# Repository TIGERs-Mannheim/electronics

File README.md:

# TIGERs Mannheim Open-Source Electronics

This repository contains electronics for our robots and our base station. There is one folder for each released version.  
Have a look at our [2020 ETDP](https://tigers-mannheim.de/download/tdps/2020_ETDP_TIGERS.pdf) which contains many details about design decisions and lessons learned over the last 10 years.

The following files are present for each release.

### EAGLE
Electronics are designed with [Autodesk EAGLE](https://www.autodesk.com/education/free-software/eagle) which is available for free for students.
This folder contains all schematics (.sch) and board (.brd) files.

### KiCad9
EAGLE files converted to KiCad version 9. Files got only a light cleanup pass.
Note that no PCBs were ever produced using these files. The EAGLE files are still the ground truth.

### PDF
All schematics are also available as PDF files. This makes it easier to view them without a need to install EAGLE.

### CAM
CAM jobs for EAGLE. Used to produce manufacturing data from board files.

### Gerber
Production ready zip packages for all boards. Most PCB production services directly accept gerber files.

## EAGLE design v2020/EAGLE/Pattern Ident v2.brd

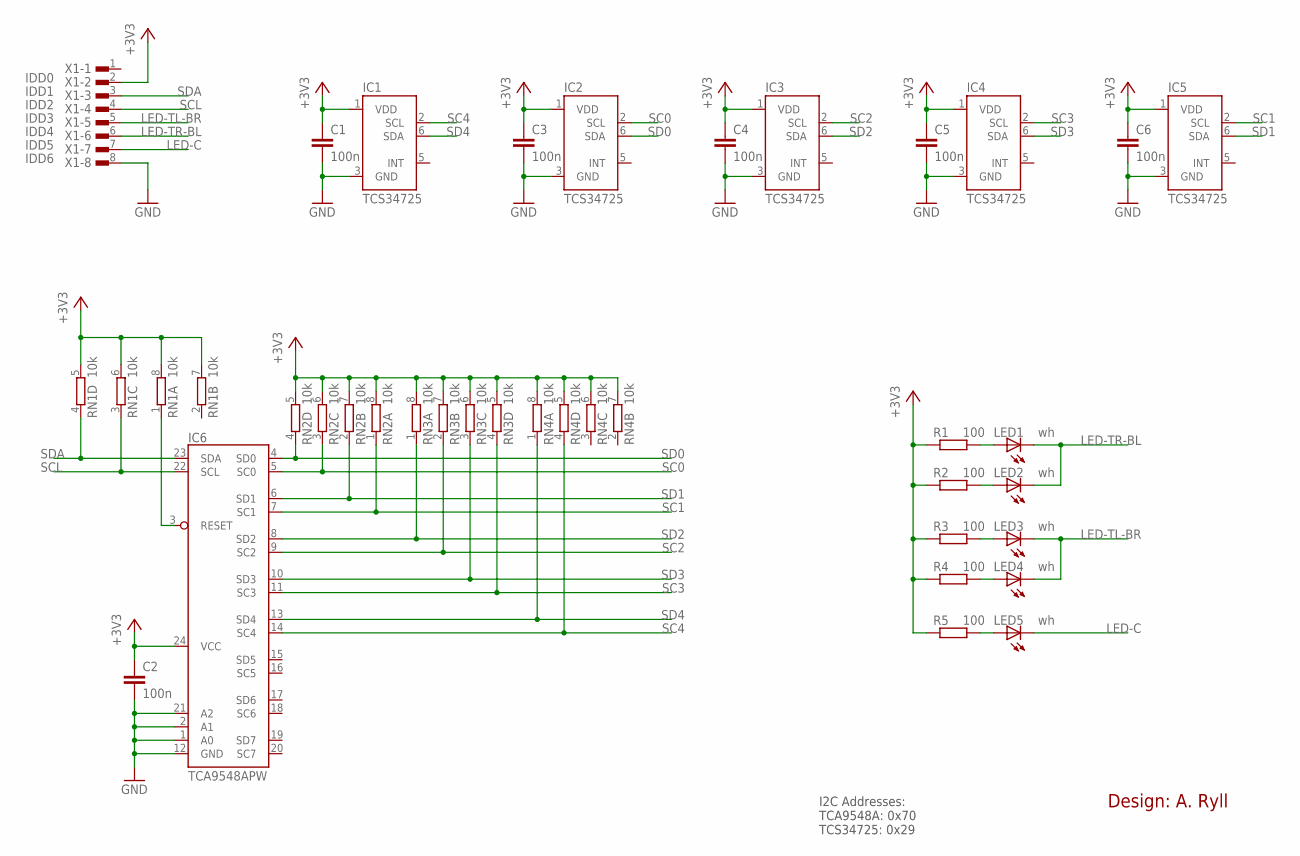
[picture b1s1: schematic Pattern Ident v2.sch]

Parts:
C1, C2, C3, C4, C5, C6: 100n; C0603
IC1, IC2, IC3, IC4, IC5: TCS34725; DFN6
IC6: TCA9548APW; TSSOP24
LED1, LED2, LED3, LED4, LED5: wh; CHIPLED_1206
R1, R2, R3, R4, R5: 100; R0603
RN1, RN2, RN3, RN4: 10k; EXB28V
X1: TE-FPC-1MM-8H; TE-84952-8

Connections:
+3V3: C1.1, C2.1, C3.1, C4.1, C5.1, C6.1, IC1.1 (VDD), IC2.1 (VDD), IC3.1 (VDD), IC4.1 (VDD), IC5.1 (VDD), IC6.24 (VCC), R1.1, R2.1, R3.1, R4.1, R5.1, RN1.5 (2), RN1.6 (2), RN1.7 (2), RN1.8 (2), RN2.5 (2), RN2.6 (2), RN2.7 (2), RN2.8 (2), RN3.5 (2), RN3.6 (2), RN3.7 (2), RN3.8 (2), RN4.5 (2), RN4.6 (2), RN4.7 (2), RN4.8 (2), X1.2
GND: C1.2, C2.2, C3.2, C4.2, C5.2, C6.2, IC1.3 (GND), IC2.3 (GND), IC3.3 (GND), IC4.3 (GND), IC5.3 (GND), IC6.1 (A0), IC6.2 (A1), IC6.12 (GND), IC6.21 (A2), X1.8
LED-C: LED5.C, X1.7
LED-TL-BR: LED3.C, LED4.C, X1.5
LED-TR-BL: LED1.C, LED2.C, X1.6
unnamed: LED1.A, R1.2
unnamed: LED2.A, R2.2
unnamed: LED3.A, R3.2
unnamed: LED4.A, R4.2
unnamed: LED5.A, R5.2
RESET: IC6.3 (RESET), RN1.1
SC0: IC2.2 (SCL), IC6.5 (SC0), RN2.3 (1)
SC1: IC5.2 (SCL), IC6.7 (SC1), RN2.1
SC2: IC3.2 (SCL), IC6.9 (SC2), RN3.2 (1)
SC3: IC4.2 (SCL), IC6.11 (SC3), RN3.4 (1)
SC4: IC1.2 (SCL), IC6.14 (SC4), RN4.4 (1)
SCL: IC6.22 (SCL), RN1.3 (1), X1.4
SD0: IC2.6 (SDA), IC6.4 (SD0), RN2.4 (1)
SD1: IC5.6 (SDA), IC6.6 (SD1), RN2.2 (1)
SD2: IC3.6 (SDA), IC6.8 (SD2), RN3.1
SD3: IC4.6 (SDA), IC6.10 (SD3), RN3.3 (1)
SD4: IC1.6 (SDA), IC6.13 (SD4), RN4.1
SDA: IC6.23 (SDA), RN1.4 (1), X1.3

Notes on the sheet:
I2C Addresses: TCA9548A: 0x70 TCS34725: 0x29
Design: A. Ryll

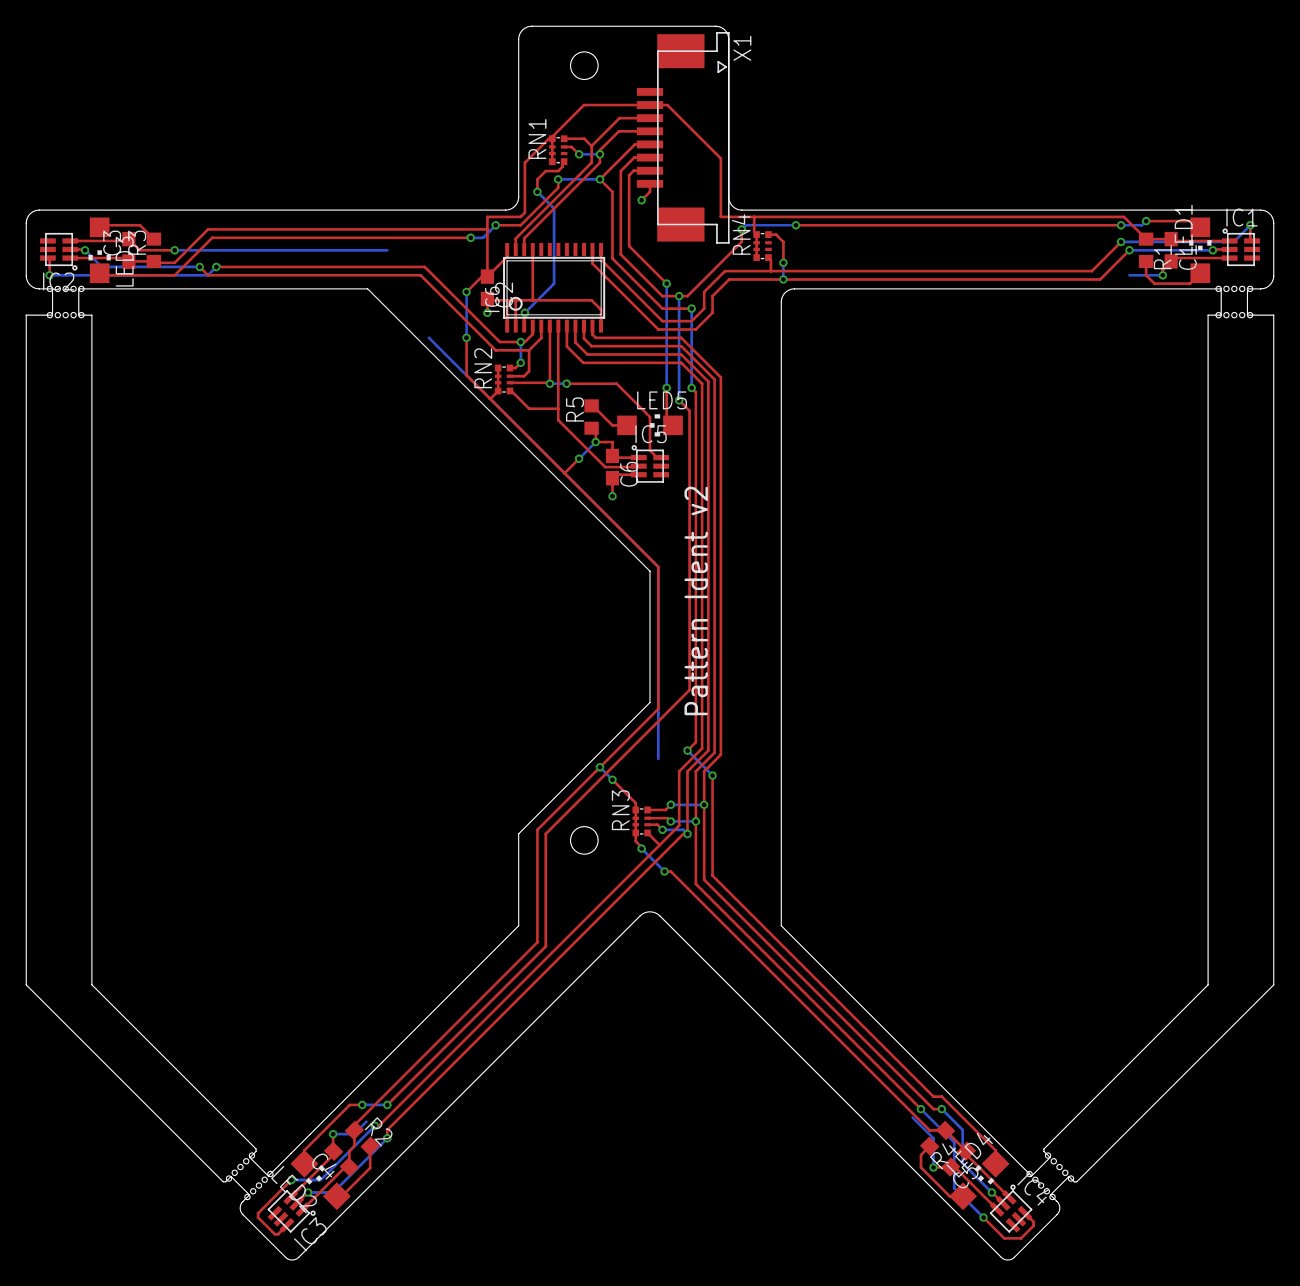
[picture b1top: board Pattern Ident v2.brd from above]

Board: 2 copper layers, 95.0 x 94.0 mm, 27 parts (0 on the bottom side), 23 nets.

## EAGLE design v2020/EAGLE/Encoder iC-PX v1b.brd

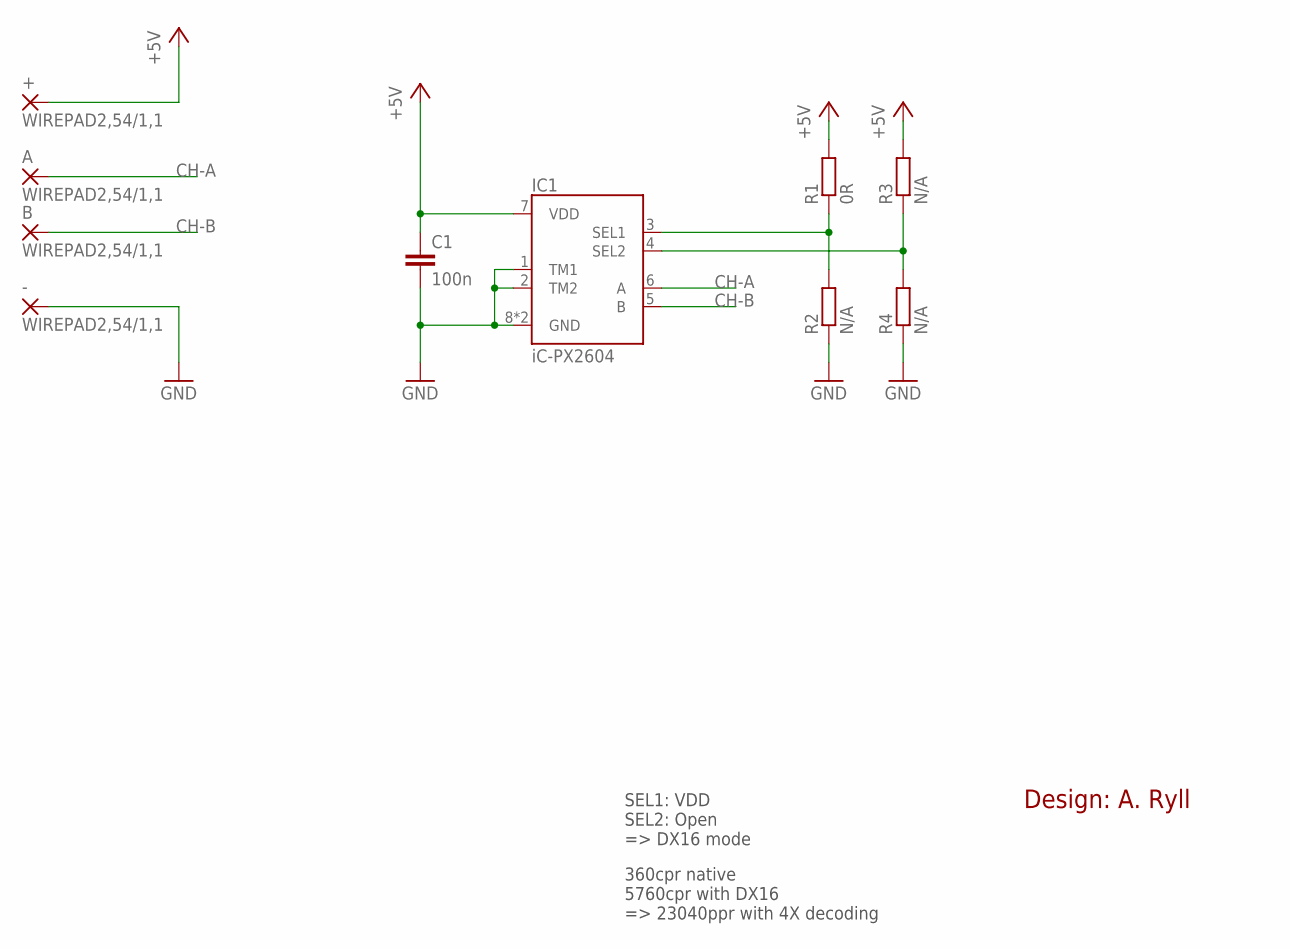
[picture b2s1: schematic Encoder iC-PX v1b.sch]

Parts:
+: WIREPAD2,54/1,1; 2,54/1,1
-: WIREPAD2,54/1,1; 2,54/1,1
A: WIREPAD2,54/1,1; 2,54/1,1
B: WIREPAD2,54/1,1; 2,54/1,1
C1: 100n; C0603
IC1: iC-PX2604; ODFN8-3X3
R1: 0R; R0603
R2, R3, R4: N/A; R0603

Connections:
+5V: +.1, C1.1, IC1.7 (VDD), R1.2, R3.2
CH-A: A.1, IC1.6 (A)
CH-B: B.1, IC1.5 (B)
GND: -.1, C1.2, IC1.1 (TM1), IC1.2 (TM2), IC1.8 (GND), IC1.BP (GND), R2.1, R4.1
SEL1: IC1.3 (SEL1), R1.1, R2.2
SEL2: IC1.4 (SEL2), R3.1, R4.2

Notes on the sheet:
SEL1: VDD SEL2: Open => DX16 mode
360cpr native 5760cpr with DX16 => 23040ppr with 4X decoding
Design: A. Ryll

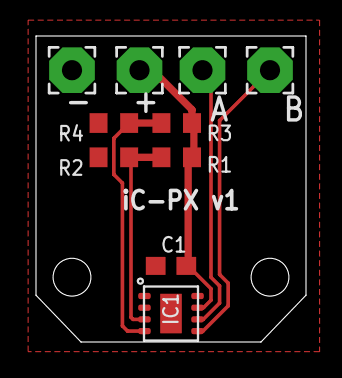
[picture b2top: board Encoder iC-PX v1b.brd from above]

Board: 2 copper layers, 15.0 x 17.0 mm, 10 parts (0 on the bottom side), 6 nets.

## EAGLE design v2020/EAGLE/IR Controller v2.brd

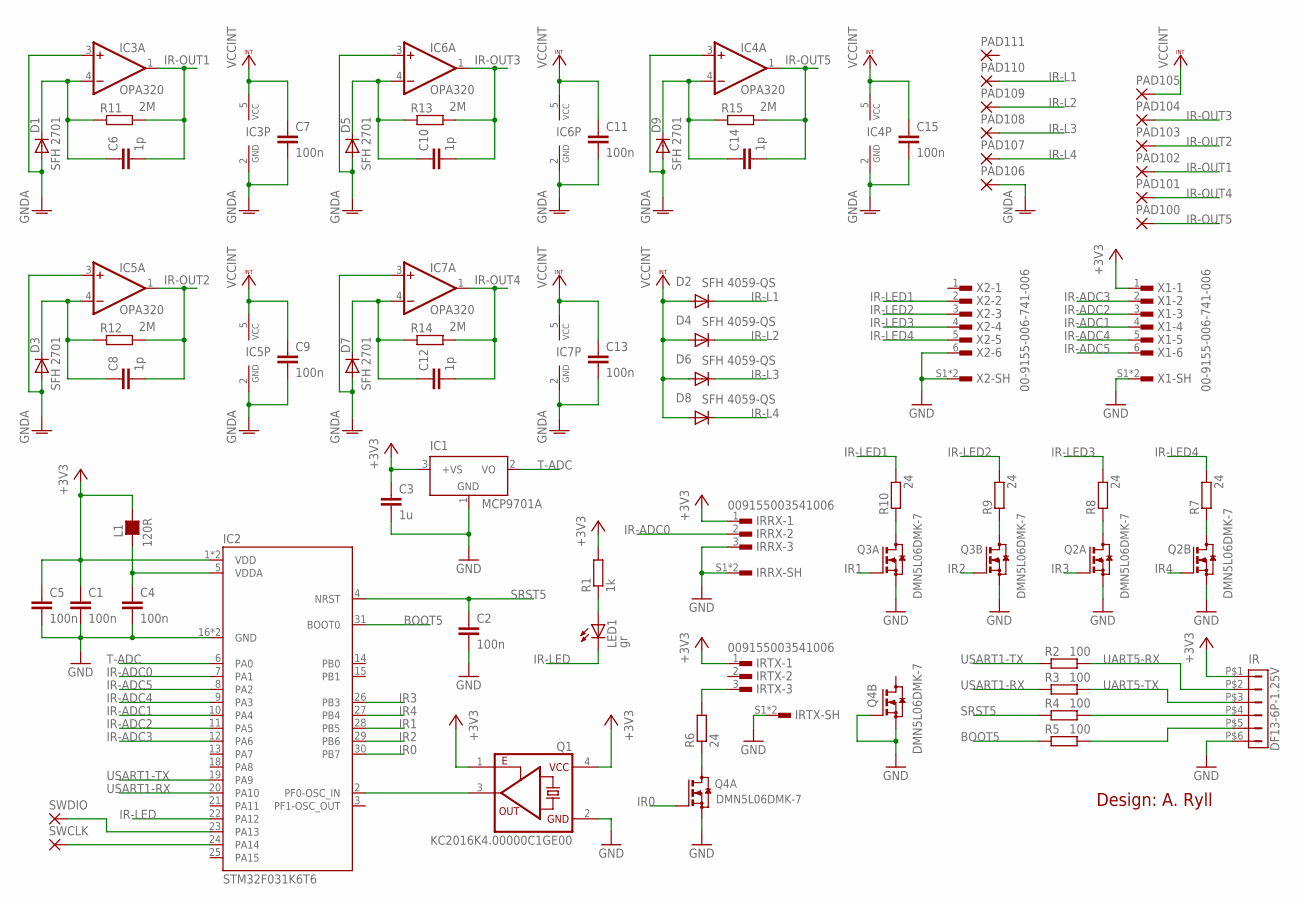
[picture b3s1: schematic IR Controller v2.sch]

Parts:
C1, C2, C4, C5, C7, C9, C11, C13, C15: 100n; C0603
C3: 1u; C0603
C6, C8, C10, C12, C14: 1p; C0603
D1, D3, D5, D7, D9: SFH 2701; LED-GULL
D2, D4, D6, D8: SFH 4059-QS; LED-GULL
IC1: MCP9701A; TO92
IC2: STM32F031K6T6; LQFP32-ST
IC3, IC4, IC5, IC6, IC7: OPA320; SOT23-5
IR: DF13-6P-1.25V; DF13C-6P-1.25V
IRRX: 009155003541006; AVX-CON3
IRTX: 009155003541006; AVX-CON3
L1: 120R; L0603
LED1: gr; CHIP-LED0603
PAD100, PAD101, PAD102, PAD103, PAD104, PAD105, PAD106, PAD107, PAD108, PAD109, PAD110, PAD111: WIREPADSMD1,4-3; SMD1,4-3
Q1: KC2016K4.00000C1GE00; OSCI-KC2016
Q2, Q3, Q4: DMN5L06DMK-7; SOT26
R1: 1k; R0603
R2, R3, R4, R5: 100; R0805
R6, R7, R8, R9, R10: 24; R0805
R11, R12, R13, R14, R15: 2M; R0603
SWCLK: WIREPADSMD1,27-254; SMD1,27-2,54
SWDIO: WIREPADSMD1,27-254; SMD1,27-2,54
X1, X2: 00-9155-006-741-006; AVX-CON6-2MM

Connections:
+3V3: C1.1, C3.1, C5.1, IC1.3 (+VS), IC2.1 (VDD), IC2.17 (VDD), IR.P$1 (1), IRRX.1, IRTX.1, L1.2, Q1.1 (OE), Q1.4 (VCC), R1.2, X1.1
BOOT5: IC2.31 (BOOT0), R5.1
GND: C1.2, C2.2, C3.2, C4.2, C5.2, IC1.1 (GND), IC2.16 (GND), IC2.32 (GND), IR.P$6 (6), IRRX.3, IRRX.S1, IRRX.S2, IRTX.S1, IRTX.S2, Q1.2 (GND), Q2.1 (S), Q2.4 (S), Q3.1 (S), Q3.4 (S), Q4.1 (S), Q4.2 (G), Q4.4 (S), X1.S1, X1.S2, X2.6, X2.S1, X2.S2
GNDA: C7.2, C9.2, C11.2, C13.2, C15.2, D1.A, D3.A, D5.A, D7.A, D9.A, IC3.2 (GND), IC3.3 (+IN), IC4.2 (GND), IC4.3 (+IN), IC5.2 (GND), IC5.3 (+IN), IC6.2 (GND), IC6.3 (+IN), IC7.2 (GND), IC7.3 (+IN), PAD106.1
IR0: IC2.30 (PB7), Q4.5 (G)
IR1: IC2.28 (PB5), Q3.5 (G)
IR2: IC2.29 (PB6), Q3.2 (G)
IR3: IC2.26 (PB3), Q2.5 (G)
IR4: IC2.27 (PB4), Q2.2 (G)
IR-ADC0: IC2.7 (PA1), IRRX.2
IR-ADC1: IC2.10 (PA4), X1.4
IR-ADC2: IC2.11 (PA5), X1.3
IR-ADC3: IC2.12 (PA6), X1.2
IR-ADC4: IC2.9 (PA3), X1.5
IR-ADC5: IC2.8 (PA2), X1.6
IR-L1: D2.C, PAD110.1
IR-L2: D4.C, PAD109.1
IR-L3: D6.C, PAD108.1
IR-L4: D8.C, PAD107.1
IR-LED: IC2.22 (PA12), LED1.C
IR-LED1: R10.2, X2.2
IR-LED2: R9.2, X2.3
IR-LED3: R8.2, X2.4
IR-LED4: R7.2, X2.5
IR-OUT1: C6.2, IC3.1 (OUT), PAD102.1, R11.2
IR-OUT2: C8.2, IC5.1 (OUT), PAD103.1, R12.2
IR-OUT3: C10.2, IC6.1 (OUT), PAD104.1, R13.2
IR-OUT4: C12.2, IC7.1 (OUT), PAD101.1, R14.2
IR-OUT5: C14.2, IC4.1 (OUT), PAD100.1, R15.2
unnamed: IR.P$4 (4), R4.2
unnamed: IC2.23 (PA13), SWDIO.1
unnamed: IR.P$5 (5), R5.2
unnamed: IC2.24 (PA14), SWCLK.1
unnamed: C14.1, D9.C, IC4.4 (-IN), R15.1
unnamed: C10.1, D5.C, IC6.4 (-IN), R13.1
unnamed: C8.1, D3.C, IC5.4 (-IN), R12.1
unnamed: Q3.3 (D), R10.1
unnamed: C6.1, D1.C, IC3.4 (-IN), R11.1
unnamed: IC2.2 (PF0-OSC_IN), Q1.3 (FO)
unnamed: C4.1, IC2.5 (VDDA), L1.1
unnamed: IRTX.3, R6.2
unnamed: C12.1, D7.C, IC7.4 (-IN), R14.1
unnamed: Q4.3 (D), R6.1
unnamed: Q3.6 (D), R9.1
unnamed: Q2.3 (D), R8.1
unnamed: Q2.6 (D), R7.1
unnamed: LED1.A, R1.1
SRST5: C2.1, IC2.4 (NRST), R4.1
T-ADC: IC1.2 (VO), IC2.6 (PA0)
UART5-RX: IR.P$2 (2), R2.2
UART5-TX: IR.P$3 (3), R3.2
USART1-RX: IC2.20 (PA10), R3.1
USART1-TX: IC2.19 (PA9), R2.1
VCCINT: C7.1, C9.1, C11.1, C13.1, C15.1, D2.A, D4.A, D6.A, D8.A, IC3.5 (VCC), IC4.5 (VCC), IC5.5 (VCC), IC6.5 (VCC), IC7.5 (VCC), PAD105.1

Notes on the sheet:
Design: A. Ryll

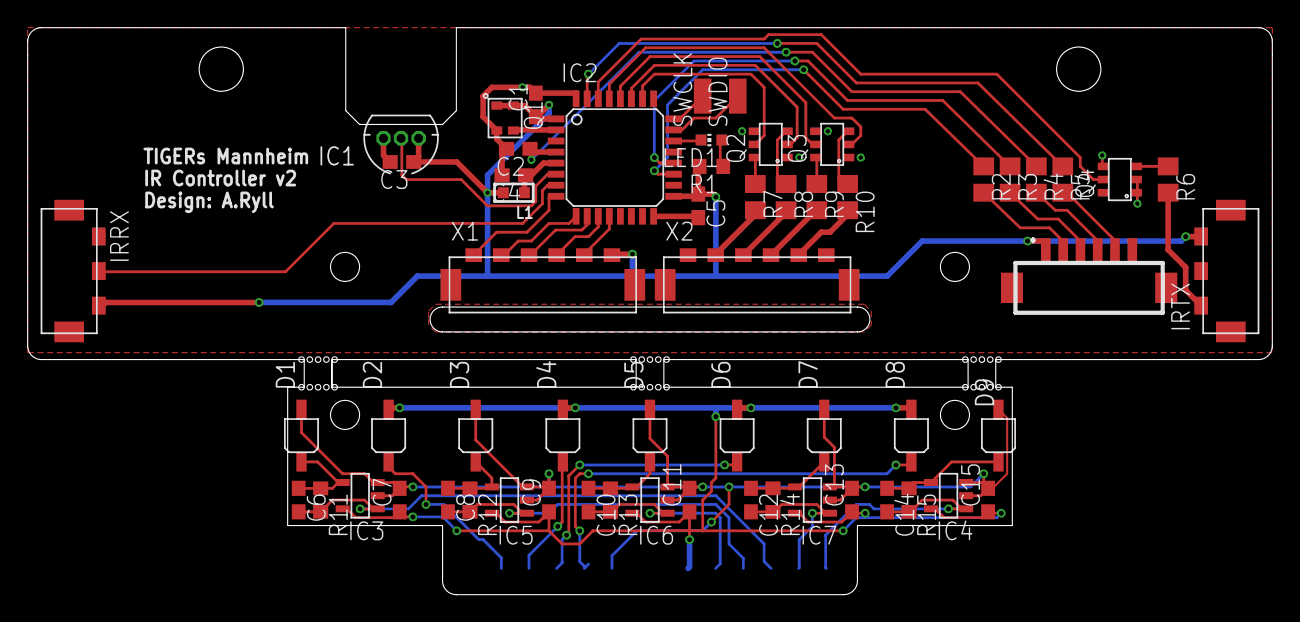
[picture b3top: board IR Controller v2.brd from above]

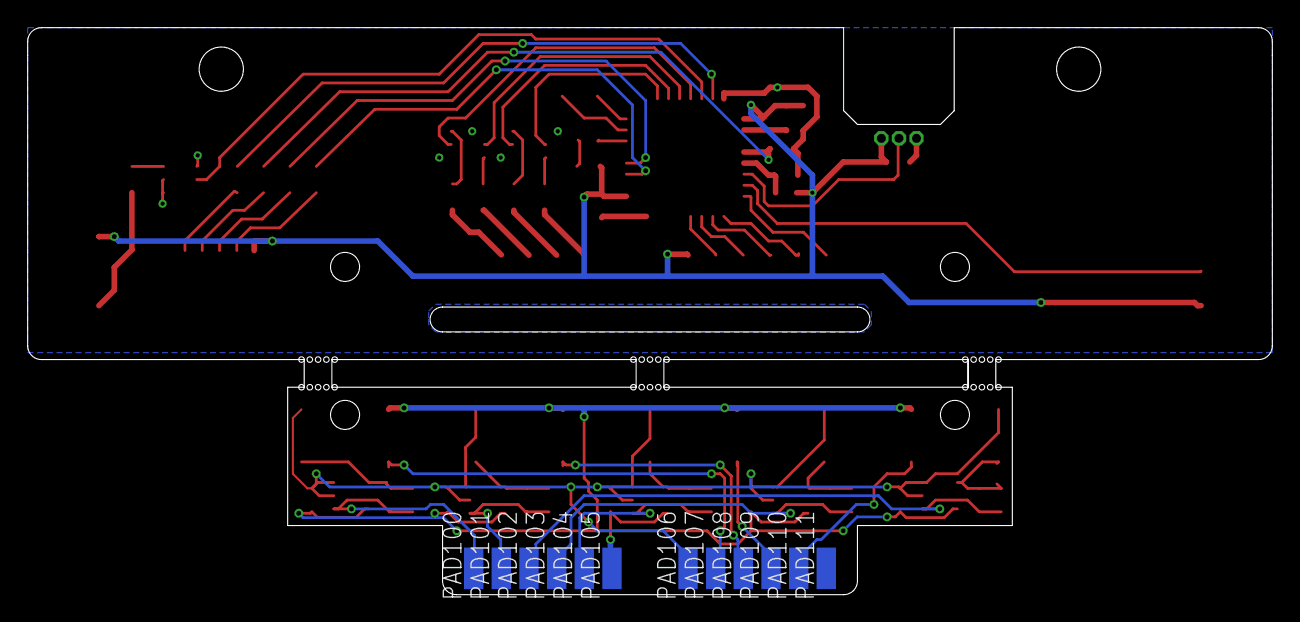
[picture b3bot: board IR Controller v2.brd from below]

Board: 2 copper layers, 90.0 x 41.0 mm, 71 parts (12 on the bottom side), 54 nets.

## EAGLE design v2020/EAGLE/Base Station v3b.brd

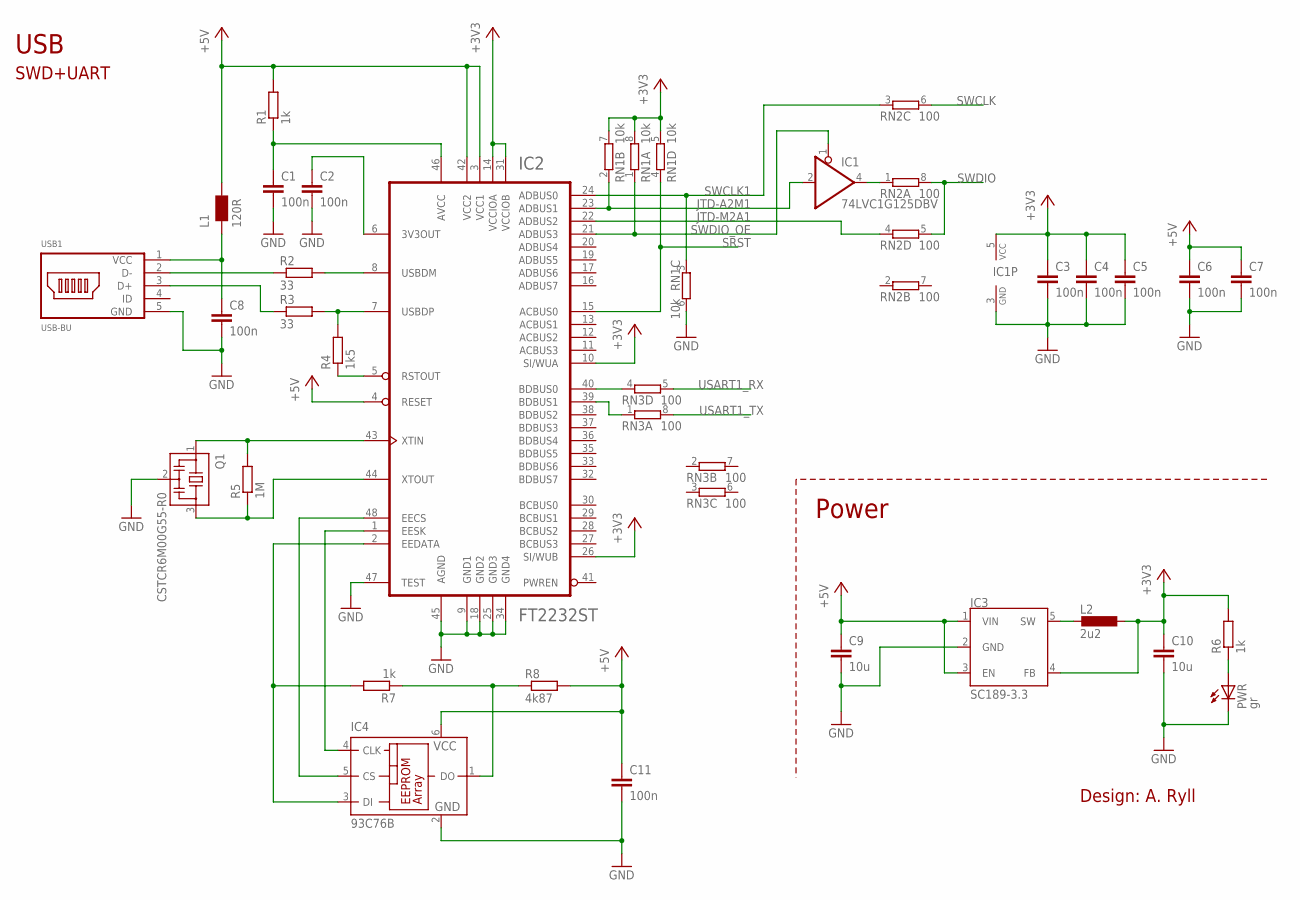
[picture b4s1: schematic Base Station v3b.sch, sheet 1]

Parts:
C1, C2, C3, C4, C5, C6, C7, C8, C11: 100n; C0603
C9, C10: 10u; C0603
IC1: 74LVC1G125DBV; SOT23-5
IC2: FT2232ST; LQFP48-ST
IC3: SC189-3.3; SOT23-5
IC4: 93C76B; SOT23-6
L1: 120R; 0603
L2: 2u2; IHLP1616
PWR: gr; CHIP-LED0603
Q1: CSTCR6M00G55-R0; CSTCR6M
R1, R6, R7: 1k; R0603
R2, R3: 33; R0603
R4: 1k5; R0603
R5: 1M; R0603
R8: 4k87; R0603
RN1: 10k; EXB28V
RN2, RN3: 100; EXB28V
USB1: USB-BU; USB-BMICRO

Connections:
+3V3: C3.1, C4.1, C5.1, C10.1, IC1.5 (VCC), IC2.10 (SI/WUA), IC2.14 (VCCIOA), IC2.26 (SI/WUB), IC2.31 (VCCIOB), IC3.4 (FB), L2.P$1 (1), R6.2, RN1.5 (2), RN1.7 (2), RN1.8 (2); also elsewhere on the board
+5V: C6.1, C7.1, C9.1, C11.1, IC2.3 (VCC1), IC2.4 (RESET), IC2.42 (VCC2), IC3.1 (VIN), IC3.3 (EN), IC4.6 (VCC), L1.2, R1.2, R8.2; also elsewhere on the board
GND: C1.2, C2.2, C3.2, C4.2, C5.2, C6.2, C7.2, C8.2, C9.2, C10.2, C11.2, IC1.3 (GND), IC2.9 (GND1), IC2.18 (GND2), IC2.25 (GND3), IC2.34 (GND4), IC2.45 (AGND), IC2.47 (TEST), IC3.2 (GND), IC4.2 (GND), PWR.C, Q1.2, RN1.6 (2), USB1.5 (GND); also elsewhere on the board
JTD-A2M1: IC1.2 (I), IC2.23 (ADBUS1), RN1.2 (1)
JTD-M2A1: IC2.22 (ADBUS2), RN2.4 (1)
unnamed: IC2.48 (EECS), IC4.5 (CS)
unnamed: IC2.1 (EESK), IC4.4 (CLK)
unnamed: IC2.2 (EEDATA), IC4.3 (DI), R7.2
unnamed: IC2.44 (XTOUT), Q1.3, R5.1
unnamed: IC4.1 (DO), R7.1, R8.1
unnamed: PWR.A, R6.1
unnamed: IC1.4 (O), RN2.1
unnamed: IC2.40 (BDBUS0), RN3.4 (1)
unnamed: IC2.39 (BDBUS1), RN3.1
unnamed: IC2.7 (USBDP), R3.2, R4.2
unnamed: IC2.8 (USBDM), R2.2
unnamed: IC2.5 (RSTOUT), R4.1
unnamed: C2.1, IC2.6 (3V3OUT)
unnamed: C8.1, L1.1, USB1.1 (VCC)
unnamed: R2.1, USB1.2 (D-)
unnamed: R3.1, USB1.3 (D+)
unnamed: C1.1, IC2.46 (AVCC), R1.1
unnamed: IC2.43 (XTIN), Q1.1, R5.2
SRST: IC2.15 (ACBUS0), RN1.4 (1); also elsewhere on the board
SW-OUT: IC3.5 (SW), L2.P$2 (2)
SWCLK: RN2.6 (2); also elsewhere on the board
SWCLK1: IC2.24 (ADBUS0), RN1.3 (1), RN2.3 (1)
SWDIO: RN2.5 (2), RN2.8 (2); also elsewhere on the board
SWDIO_OE: IC1.1 (OE), IC2.21 (ADBUS3), RN1.1
USART1_RX: RN3.5 (2); also elsewhere on the board
USART1_TX: RN3.8 (2); also elsewhere on the board

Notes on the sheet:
Power
Design: A. Ryll
USB
SWD+UART

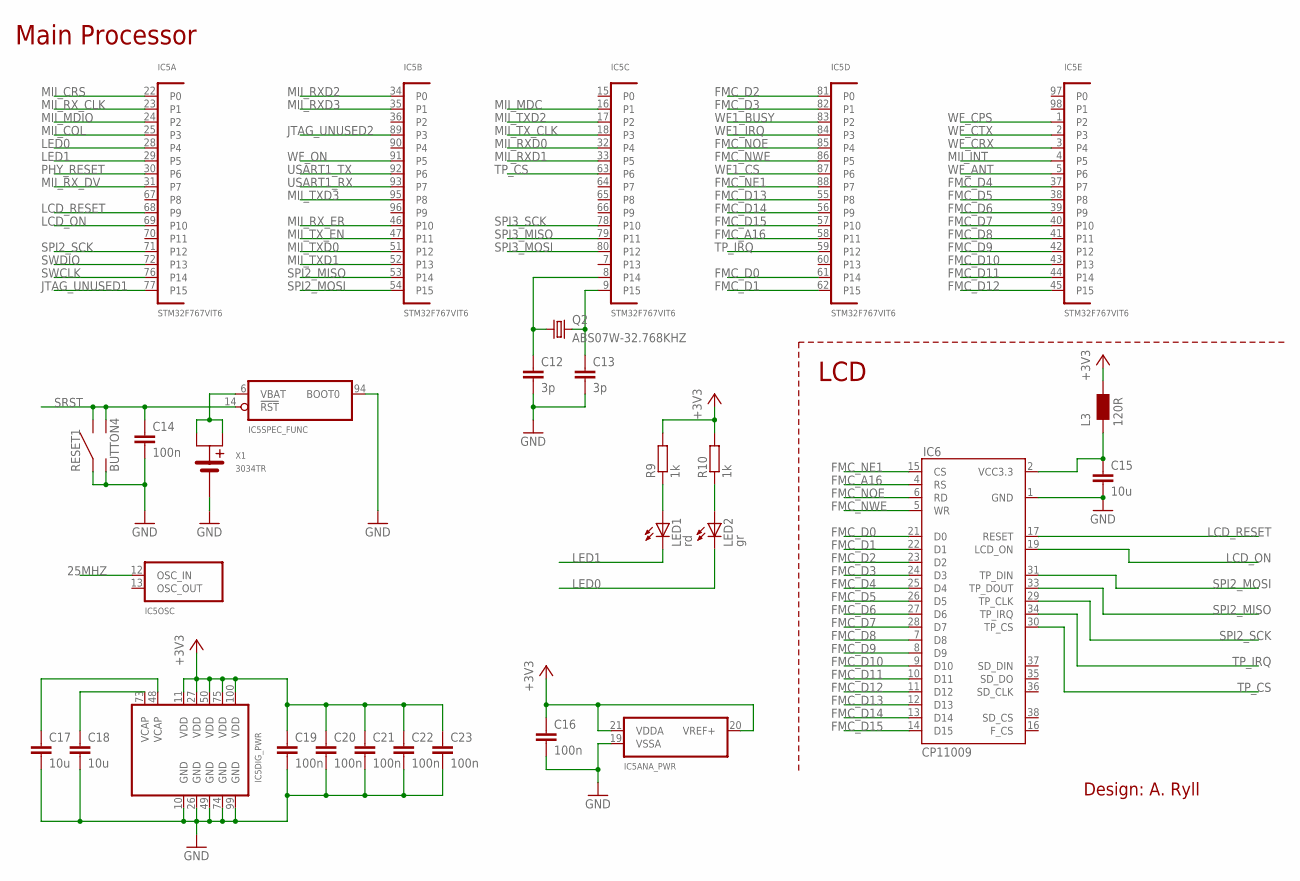
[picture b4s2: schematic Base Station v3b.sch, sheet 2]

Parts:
C12, C13: 3p; C0603
C14, C16, C19, C20, C21, C22, C23: 100n; C0603
C15, C17, C18: 10u; C0603
IC5: STM32F767VIT6; LQFP100-ST
IC6: CP11009; CP11009-THX
L3: 120R; 0603
LED1: rd; CHIP-LED0603
LED2: gr; CHIP-LED0603
Q2: ABS07W-32.768KHZ; CRYSTAL-07W
R9, R10: 1k; R0603
RESET1: BUTTON4
X1: 3034TR; CR2025

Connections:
25MHZ: IC5.12 (OSC_IN); also elsewhere on the board
+3V3: C16.1, C19.1, C20.1, C21.1, C22.1, C23.1, IC5.11 (VDD), IC5.20 (VREF+), IC5.21 (VDDA), IC5.27 (VDD), IC5.50 (VDD), IC5.75 (VDD), IC5.100 (VDD), L3.2, R9.2, R10.2; also elsewhere on the board
FMC_A16: IC5.58 (P11), IC6.4 (RS)
FMC_D0: IC5.61 (P14), IC6.21 (D0)
FMC_D1: IC5.62 (P15), IC6.22 (D1)
FMC_D2: IC5.81 (P0), IC6.23 (D2)
FMC_D3: IC5.82 (P1), IC6.24 (D3)
FMC_D4: IC5.37 (P7), IC6.25 (D4)
FMC_D5: IC5.38 (P8), IC6.26 (D5)
FMC_D6: IC5.39 (P9), IC6.27 (D6)
FMC_D7: IC5.40 (P10), IC6.28 (D7)
FMC_D8: IC5.41 (P11), IC6.7 (D8)
FMC_D9: IC5.42 (P12), IC6.8 (D9)
FMC_D10: IC5.43 (P13), IC6.9 (D10)
FMC_D11: IC5.44 (P14), IC6.10 (D11)
FMC_D12: IC5.45 (P15), IC6.11 (D12)
FMC_D13: IC5.55 (P8), IC6.12 (D13)
FMC_D14: IC5.56 (P9), IC6.13 (D14)
FMC_D15: IC5.57 (P10), IC6.14 (D15)
FMC_NE1: IC5.88 (P7), IC6.15 (CS)
FMC_NOE: IC5.85 (P4), IC6.6 (RD)
FMC_NWE: IC5.86 (P5), IC6.5 (WR)
GND: C12.2, C13.2, C14.2, C15.2, C16.2, C17.2, C18.2, C19.2, C20.2, C21.2, C22.2, C23.2, IC5.10 (GND), IC5.19 (VSSA), IC5.26 (GND), IC5.49 (GND), IC5.74 (GND), IC5.94 (BOOT0), IC5.99 (GND), IC6.1 (GND), RESET1.1, RESET1.2, X1.GND; also elsewhere on the board
JTAG_UNUSED1: IC5.77 (P15)
JTAG_UNUSED2: IC5.89 (P3)
LCD_ON: IC5.69 (P10), IC6.19 (LCD_ON)
LCD_RESET: IC5.68 (P9), IC6.17 (RESET)
LED0: IC5.28 (P4), LED2.C
LED1: IC5.29 (P5), LED1.C
MII_COL: IC5.25 (P3); also elsewhere on the board
MII_CRS: IC5.22 (P0); also elsewhere on the board
MII_INT: IC5.4 (P5); also elsewhere on the board
MII_MDC: IC5.16 (P1); also elsewhere on the board
MII_MDIO: IC5.24 (P2); also elsewhere on the board
MII_RXD0: IC5.32 (P4); also elsewhere on the board
MII_RXD1: IC5.33 (P5); also elsewhere on the board
MII_RXD2: IC5.34 (P0); also elsewhere on the board
MII_RXD3: IC5.35 (P1); also elsewhere on the board
MII_RX_CLK: IC5.23 (P1); also elsewhere on the board
MII_RX_DV: IC5.31 (P7); also elsewhere on the board
MII_RX_ER: IC5.46 (P10); also elsewhere on the board
MII_TXD0: IC5.51 (P12); also elsewhere on the board
MII_TXD1: IC5.52 (P13); also elsewhere on the board
MII_TXD2: IC5.17 (P2); also elsewhere on the board
MII_TXD3: IC5.95 (P8); also elsewhere on the board
MII_TX_CLK: IC5.18 (P3); also elsewhere on the board
MII_TX_EN: IC5.47 (P11); also elsewhere on the board
unnamed: C18.1, IC5.73 (VCAP)
unnamed: C17.1, IC5.48 (VCAP)
unnamed: LED2.A, R10.1
unnamed: LED1.A, R9.1
unnamed: C15.1, IC6.2 (VCC3.3), L3.1
OSC32_IN: C12.1, IC5.8 (P14), Q2.1
OSC32_OUT: C13.1, IC5.9 (P15), Q2.2
PHY_RESET: IC5.30 (P6); also elsewhere on the board
SPI2_MISO: IC5.53 (P14), IC6.33 (TP_DOUT)
SPI2_MOSI: IC5.54 (P15), IC6.31 (TP_DIN)
SPI2_SCK: IC5.71 (P12), IC6.29 (TP_CLK)
SPI3_MISO: IC5.79 (P11); also elsewhere on the board
SPI3_MOSI: IC5.80 (P12); also elsewhere on the board
SPI3_SCK: IC5.78 (P10); also elsewhere on the board
SRST: C14.1, IC5.14 (!RST), RESET1.3, RESET1.4; also elsewhere on the board
SWCLK: IC5.76 (P14); also elsewhere on the board
SWDIO: IC5.72 (P13); also elsewhere on the board
TP_CS: IC5.63 (P6), IC6.30 (TP_CS)
TP_IRQ: IC5.59 (P12), IC6.34 (TP_IRQ)
USART1_RX: IC5.93 (P7); also elsewhere on the board
USART1_TX: IC5.92 (P6); also elsewhere on the board
VBAT: IC5.6 (VBAT), X1.POS1, X1.POS2
WF1_BUSY: IC5.83 (P2); also elsewhere on the board
WF1_CS: IC5.87 (P6); also elsewhere on the board
WF1_IRQ: IC5.84 (P3); also elsewhere on the board
WF_ANT: IC5.5 (P6); also elsewhere on the board
WF_CPS: IC5.1 (P2); also elsewhere on the board
WF_CRX: IC5.3 (P4); also elsewhere on the board
WF_CTX: IC5.2 (P3); also elsewhere on the board
WF_ON: IC5.91 (P5); also elsewhere on the board

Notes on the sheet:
Main Processor
LCD
Design: A. Ryll

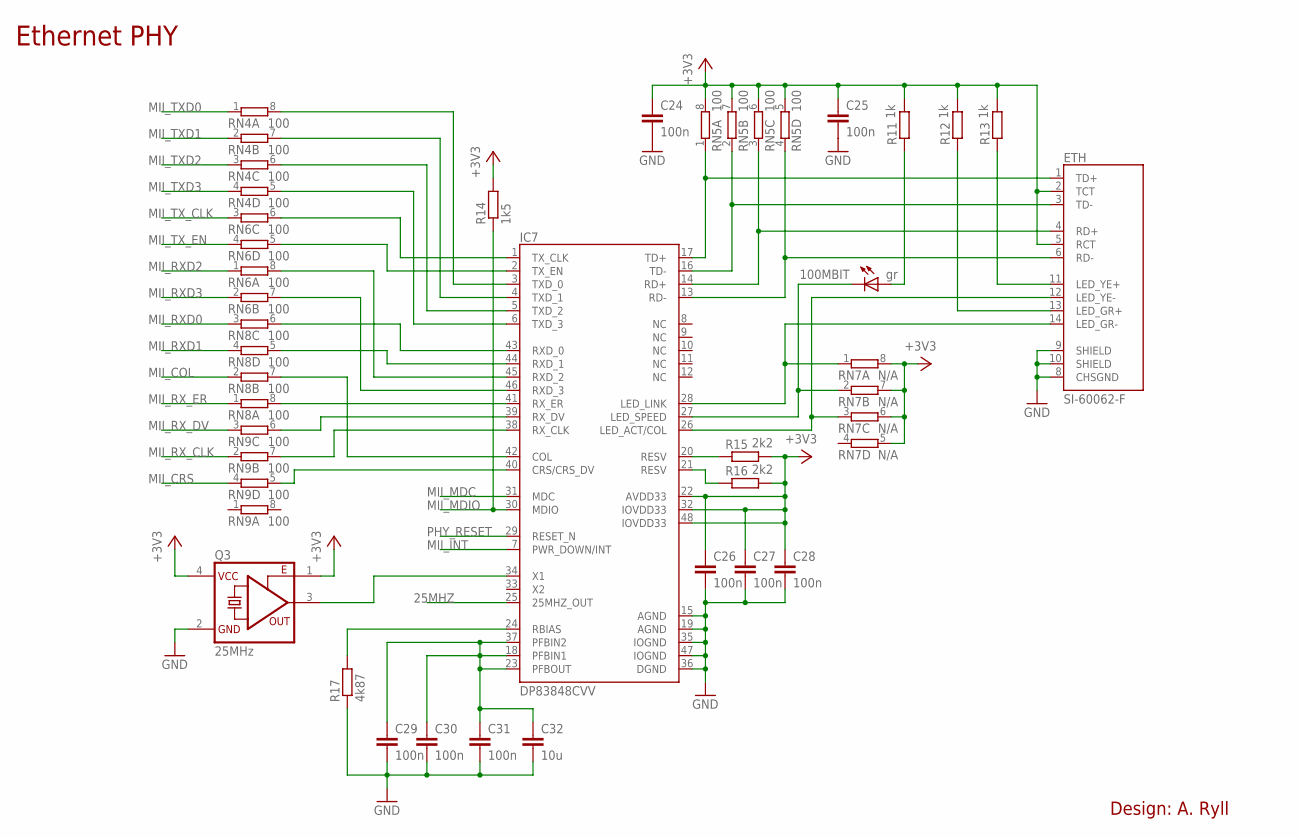
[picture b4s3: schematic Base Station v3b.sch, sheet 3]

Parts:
100MBIT: gr; CHIP-LED0603
C24, C25, C26, C27, C28, C29, C30, C31: 100n; C0603
C32: 10u; C0603
ETH: SI-60062-F; RJ45-LED
IC7: DP83848CVV; LQFP48
Q3: 25MHz; 7X
R11, R12, R13: 1k; R0603
R14: 1k5; R0603
R15, R16: 2k2; R0603
R17: 4k87; R0603
RN4, RN5, RN6, RN8, RN9: 100; EXB28V
RN7: N/A; EXB28V

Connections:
25MHZ: IC7.25 (25MHZ_OUT); also elsewhere on the board
+3V3: C24.1, C25.1, C26.1, C27.1, C28.1, ETH.2 (TCT), ETH.5 (RCT), IC7.22 (AVDD33), IC7.32 (IOVDD33), IC7.48 (IOVDD33), Q3.1 (OE), Q3.4 (VCC), R11.2, R12.2, R13.2, R14.2, R15.2, R16.2, RN5.5 (2), RN5.6 (2), RN5.7 (2), RN5.8 (2), RN7.5 (2), RN7.6 (2), RN7.7 (2), RN7.8 (2); also elsewhere on the board
GND: C24.2, C25.2, C26.2, C27.2, C28.2, C29.2, C30.2, C31.2, C32.2, ETH.8 (CHSGND), ETH.9 (SHIELD), ETH.10 (SHIELD), IC7.15 (AGND), IC7.19 (AGND), IC7.35 (IOGND), IC7.36 (DGND), IC7.47 (IOGND), Q3.2 (GND), R17.1; also elsewhere on the board
MII_COL: RN8.2 (1); also elsewhere on the board
MII_CRS: RN9.4 (1); also elsewhere on the board
MII_INT: IC7.7 (PWR_DOWN/INT); also elsewhere on the board
MII_MDC: IC7.31 (MDC); also elsewhere on the board
MII_MDIO: IC7.30 (MDIO), R14.1; also elsewhere on the board
MII_RXD0: RN8.3 (1); also elsewhere on the board
MII_RXD1: RN8.4 (1); also elsewhere on the board
MII_RXD2: RN6.1; also elsewhere on the board
MII_RXD3: RN6.2 (1); also elsewhere on the board
MII_RX_CLK: RN9.2 (1); also elsewhere on the board
MII_RX_DV: RN9.3 (1); also elsewhere on the board
MII_RX_ER: RN8.1; also elsewhere on the board
MII_TXD0: RN4.1; also elsewhere on the board
MII_TXD1: RN4.2 (1); also elsewhere on the board
MII_TXD2: RN4.3 (1); also elsewhere on the board
MII_TXD3: RN4.4 (1); also elsewhere on the board
MII_TX_CLK: RN6.3 (1); also elsewhere on the board
MII_TX_EN: RN6.4 (1); also elsewhere on the board
unnamed: IC7.3 (TXD_0), RN4.8 (2)
unnamed: IC7.4 (TXD_1), RN4.7 (2)
unnamed: IC7.5 (TXD_2), RN4.6 (2)
unnamed: IC7.6 (TXD_3), RN4.5 (2)
unnamed: IC7.1 (TX_CLK), RN6.6 (2)
unnamed: IC7.2 (TX_EN), RN6.5 (2)
unnamed: IC7.45 (RXD_2), RN6.8 (2)
unnamed: IC7.46 (RXD_3), RN6.7 (2)
unnamed: IC7.43 (RXD_0), RN8.6 (2)
unnamed: IC7.44 (RXD_1), RN8.5 (2)
unnamed: IC7.42 (COL), RN8.7 (2)
unnamed: IC7.41 (RX_ER), RN8.8 (2)
unnamed: IC7.39 (RX_DV), RN9.6 (2)
unnamed: IC7.38 (RX_CLK), RN9.7 (2)
unnamed: IC7.40 (CRS/CRS_DV), RN9.5 (2)
unnamed: IC7.24 (RBIAS), R17.2
unnamed: C29.1, C30.1, C31.1, C32.1, IC7.18 (PFBIN1), IC7.23 (PFBOUT), IC7.37 (PFBIN2)
unnamed: IC7.20 (RESV), R15.1
unnamed: IC7.21 (RESV), R16.1
unnamed: ETH.12 (LED_YE-), IC7.26 (LED_ACT/COL), RN7.3 (1)
unnamed: 100MBIT.C, IC7.27 (LED_SPEED), RN7.2 (1)
unnamed: ETH.14 (LED_GR-), IC7.28 (LED_LINK), RN7.1
unnamed: ETH.6 (RD-), IC7.13 (RD-), RN5.4 (1)
unnamed: ETH.4 (RD+), IC7.14 (RD+), RN5.3 (1)
unnamed: ETH.3 (TD-), IC7.16 (TD-), RN5.2 (1)
unnamed: ETH.1 (TD+), IC7.17 (TD+), RN5.1
unnamed: 100MBIT.A, R11.1
unnamed: ETH.13 (LED_GR+), R12.1
unnamed: ETH.11 (LED_YE+), R13.1
unnamed: IC7.34 (X1), Q3.3 (FO)
PHY_RESET: IC7.29 (RESET_N); also elsewhere on the board

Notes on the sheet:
Design: A. Ryll
Ethernet PHY

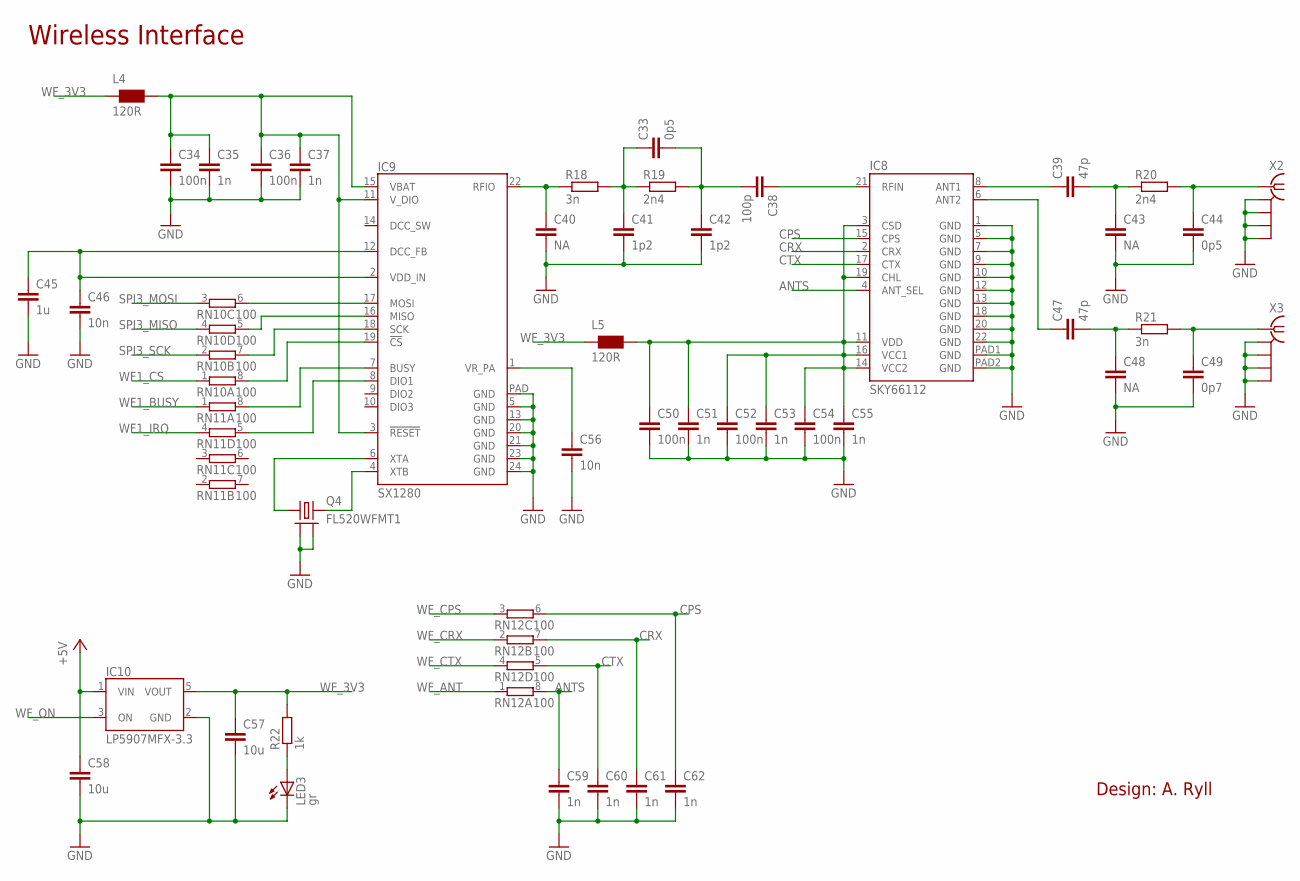
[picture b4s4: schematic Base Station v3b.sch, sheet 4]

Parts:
C33, C44: 0p5; C0402
C34, C36, C50, C52, C54: 100n; C0603
C35, C37, C51, C53, C55, C59, C60, C61, C62: 1n; C0603
C38: 100p; C0402
C39, C47: 47p; C0402
C40, C43, C48: NA; C0402
C41, C42: 1p2; C0402
C45: 1u; C0603
C46, C56: 10n; C0603
C49: 0p7; C0402
C57, C58: 10u; C0603
IC8: SKY66112; SMCM-22
IC9: SX1280; QFN24L
IC10: LP5907MFX-3.3; SOT23-5L
L4, L5: 120R; 0603
LED3: gr; CHIP-LED0603
Q4: FL520WFMT1; CRYSTAL-7M
R18, R21: 3n; R0402
R19, R20: 2n4; R0402
R22: 1k; R0603
RN10, RN11, RN12: 100; EXB28V
X2, X3: ANT-SMA-EDGERA; ANT-SMA-RA

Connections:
+5V: C58.1, IC10.1 (VIN); also elsewhere on the board
ANTS: C59.1, IC8.4 (ANT_SEL), RN12.8 (2)
CPS: C62.1, IC8.15 (CPS), RN12.6 (2)
CRX: C61.1, IC8.2 (CRX), RN12.7 (2)
CTX: C60.1, IC8.17 (CTX), RN12.5 (2)
GND: C34.2, C35.2, C36.2, C37.2, C40.2, C41.2, C42.2, C43.2, C44.2, C45.2, C46.2, C48.2, C49.2, C50.2, C51.2, C52.2, C53.2, C54.2, C55.2, C56.2, C57.2, C58.2, C59.2, C60.2, C61.2, C62.2, IC8.1 (GND), IC8.5 (GND), IC8.7 (GND), IC8.9 (GND), IC8.10 (GND), IC8.12 (GND), IC8.13 (GND), IC8.18 (GND), IC8.20 (GND), IC8.22 (GND), IC8.PAD1 (GND), IC8.PAD2 (GND), IC9.5 (GND), IC9.13 (GND), IC9.20 (GND), IC9.21 (GND), IC9.23 (GND), IC9.24 (GND), IC9.PAD (GND), IC10.2 (GND), LED3.C, Q4.2 (GND1), Q4.4 (GND2), X2.GND1 (GND), X2.GND2 (GND1), X2.GND3 (GND2), X2.GND4 (GND3), X3.GND1 (GND), X3.GND2 (GND1), X3.GND3 (GND2), X3.GND4 (GND3); also elsewhere on the board
unnamed: IC9.17 (MOSI), RN10.6 (2)
unnamed: IC9.16 (MISO), RN10.5 (2)
unnamed: IC9.18 (SCK), RN10.7 (2)
unnamed: IC9.19 (!CS), RN10.8 (2)
unnamed: IC9.7 (BUSY), RN11.8 (2)
unnamed: IC9.8 (DIO1), RN11.5 (2)
unnamed: LED3.A, R22.1
unnamed: IC9.6 (XTA), Q4.1
unnamed: IC9.4 (XTB), Q4.3 (2)
unnamed: C33.1, C41.1, R18.2, R19.1
unnamed: C33.2, C38.2, C42.1, R19.2
unnamed: C56.1, IC9.1 (VR_PA)
unnamed: C45.1, C46.1, IC9.2 (VDD_IN), IC9.12 (DCC_FB)
unnamed: C38.1, IC8.21 (RFIN)
unnamed: C39.2, C43.1, R20.1
unnamed: C44.1, R20.2, X2.C (1)
unnamed: C47.2, C48.1, R21.1
unnamed: C49.1, R21.2, X3.C (1)
unnamed: C39.1, IC8.8 (ANT1)
unnamed: C47.1, IC8.6 (ANT2)
RFIO1: C40.1, IC9.22 (RFIO), R18.1
SPI3_MISO: RN10.4 (1); also elsewhere on the board
SPI3_MOSI: RN10.3 (1); also elsewhere on the board
SPI3_SCK: RN10.2 (1); also elsewhere on the board
WF1_BUSY: RN11.1; also elsewhere on the board
WF1_CS: RN10.1; also elsewhere on the board
WF1_IRQ: RN11.4 (1); also elsewhere on the board
WF_3V3: C57.1, IC10.5 (VOUT), L4.1, L5.1, R22.2
WF_3V3FEM: C50.1, C51.1, C52.1, C53.1, C54.1, C55.1, IC8.3 (CSD), IC8.11 (VDD), IC8.14 (VCC2), IC8.16 (VCC1), IC8.19 (CHL), L5.2
WF_3V3SX: C34.1, C35.1, C36.1, C37.1, IC9.3 (!RESET), IC9.11 (V_DIO), IC9.15 (VBAT), L4.2
WF_ANT: RN12.1; also elsewhere on the board
WF_CPS: RN12.3 (1); also elsewhere on the board
WF_CRX: RN12.2 (1); also elsewhere on the board
WF_CTX: RN12.4 (1); also elsewhere on the board
WF_ON: IC10.3 (ON); also elsewhere on the board

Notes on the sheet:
Design: A. Ryll
Wireless Interface

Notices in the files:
parts and their libraries:
rc-master-smd: Copyright (C) 2007, Bob Starr
